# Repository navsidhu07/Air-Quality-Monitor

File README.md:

# ESP32 Air Quality Monitor

## Project Overview

An ESP32-based environmental monitoring system that measures
temperature, humidity, and relative air quality in real time.
The project was developed to provide a convenient way to
monitor environmental conditions before outdoor activities.

The system integrates a 16×2 LCD, LED status indicators, and
a Wi-Fi-enabled web dashboard. After developing a functional
breadboard prototype, a custom two-layer PCB was designed in
KiCad to integrate the hardware into a single board.

## Key Features

- Real-time temperature and humidity monitoring
- Relative air quality monitoring
- 16×2 LCD for local sensor readings
- LED-based air quality status indicators
- Wi-Fi-enabled web dashboard
- ESP32-based embedded firmware
- Custom two-layer PCB designed in KiCad
- Integrated USB-to-UART programming interface

## System Architecture

The ESP32 collects and processes environmental sensor data,
controls the LCD and LED indicators, and hosts a local web
server for wireless monitoring.

```mermaid
flowchart TD
    A[DHT22 Temperature and Humidity Sensor] --> C[ESP32]
    B[MQ-135 Gas Sensor] --> C

    C --> D[LCD1602 Display]
    C --> E[LED Status Indicators]
    C --> F[HTTP Web Server]

    F -->|Wi-Fi| G[Web Dashboard]
```

## Hardware - Prototype

A functional breadboard prototype was developed to establish
sensor functionality, microcontroller communication, and
system integration before transitioning to a custom PCB.

### Components

| Component | Purpose |
| --- | --- |
| ESP32 Development Board | Processing and wireless communication |
| DHT22 | Temperature and humidity sensing |
| MQ-135 | Gas sensing |
| LCD1602 | Local data visualization |
| Red, Yellow, and Green LEDs | Air quality status indication |
| Potentiometer | LCD contrast adjustment |
| Resistors | Current limiting and signal conditioning |

## Hardware - PCB Design

Following the development of the breadboard prototype, a
custom two-layer PCB was designed in KiCad to consolidate
the hardware into a single integrated system.

### Design Considerations

- ESP32-WROOM-32E module integration
- USB-to-UART communication using the CP2102N
- USB-C connectivity
- 5 V to 3.3 V voltage regulation
- Power supply decoupling capacitors
- Boot and reset circuitry
- Dedicated power and ground copper pours
- Sensor and display integration

### Schematic

### Front Copper Layer

### Back Copper Layer

The native KiCad project, schematic, PCB layout, and
associated symbol and footprint files are available
in the [Hardware](Hardware/) directory.

## Firmware

The firmware was developed in C++ using the Arduino
framework for the ESP32.

### Firmware Functionality

- Acquisition of temperature, humidity, and gas sensor readings
- Air quality classification logic using predefined thresholds
- Periodic LCD updates
- Control of LED status indicators
- Wi-Fi network connectivity
- HTTP web server for wireless monitoring
- JSON-based data transfer to the web dashboard

### GPIO Pin Assignments

| Component | Signal | ESP32 GPIO |
| --- | --- | --- |
| DHT22 | Data | 23 |
| MQ-135 | Analog Output | 36 |
| LCD1602 | RS | 19 |
| LCD1602 | Enable | 18 |
| LCD1602 | D4 | 17 |
| LCD1602 | D5 | 16 |
| LCD1602 | D6 | 4 |
| LCD1602 | D7 | 21 |
| Red LED | Output | 25 |
| Yellow LED | Output | 26 |
| Green LED | Output | 27 |

The firmware source code is available in the
[Firmware](Firmware/) directory.

## Web Dashboard

The ESP32 hosts a local HTTP web server that allows users
to monitor environmental conditions through a web browser.

The dashboard was developed using HTML, CSS, and JavaScript.
Sensor readings are transferred from the ESP32 to the browser
through a JSON-based HTTP endpoint.

### Dashboard Features

- Temperature and humidity visualization
- Gas sensor readings
- Color-coded air quality status indicators
- Automatic data requests every three seconds
- Real-time clock display
- Local wireless accessibility

## Testing and Validation

The breadboard prototype was developed and tested before
transitioning to the custom PCB design.

Prototype testing focused on:

- Temperature and humidity sensor readings
- Gas sensor response
- LCD functionality
- LED status indicators
- Wi-Fi connectivity
- Web dashboard functionality

The MQ-135 is used for relative air quality monitoring
rather than calibrated gas concentration or standardized
Air Quality Index (AQI) measurements.

The current firmware uses raw ADC readings from the MQ-135.
The classification thresholds require further refinement
to align with the ESP32's default ADC range. Accurate gas
concentration measurements and classification validation
remain areas for future development.

## Firmware Setup

### Requirements

- Arduino IDE
- ESP32 board package by Espressif Systems
- DHT Sensor Library by Adafruit
- Adafruit Unified Sensor library
- LiquidCrystal library by Arduino

The WiFi and WebServer libraries are included in the
ESP32 Arduino board package.

### Installation

1. Install the Arduino IDE.
2. Install the ESP32 board package through the Boards Manager.
3. Select the appropriate ESP32 development board.
4. Install the required libraries through the Library Manager.
5. Open the firmware file from the Firmware directory.
6. Replace the Wi-Fi credential placeholders with your
   local network credentials.
7. Compile and upload the firmware to the ESP32.
8. Open the Serial Monitor at a baud rate of 115200.
9. Locate the ESP32's assigned IP address.
10. Enter the IP address into a web browser connected to
    the same network.

## Repository Structure

```
Air-Quality-Monitor/
├── Firmware/
├── Hardware/
│   ├── Air Quality Monitor.kicad_pro
│   ├── Air Quality Monitor.kicad_sch
│   ├── Air Quality Monitor.kicad_pcb
│   ├── CP2102N-A02-GQFN20.kicad_sym
│   └── WFQFN-20.kicad_mod
└── README.md
```

## Project Status

The breadboard prototype, embedded firmware, and web dashboard 
have been successfully developed and tested. The custom PCB 
schematic, layout, and routing have also been completed in KiCad. 
However, PCB fabrication and assembly have not yet been pursued 
due to limited access to the necessary soldering equipment and 
assembly resources. Future development will focus on manufacturing, 
assembling, and validating the custom PCB.

## Future Improvements

- Fabricate, assemble, and validate the custom PCB
- Refine gas sensor classification thresholds and calibration
- Implement historical sensor data logging
- Improve firmware modularity
- Design a protective enclosure
- Implement non-blocking firmware timing using `millis()`

## Tools and Technologies

- KiCad
- Arduino IDE
- C++
- ESP32
- HTML
- CSS
- JavaScript
- Wi-Fi
- HTTP
- UART

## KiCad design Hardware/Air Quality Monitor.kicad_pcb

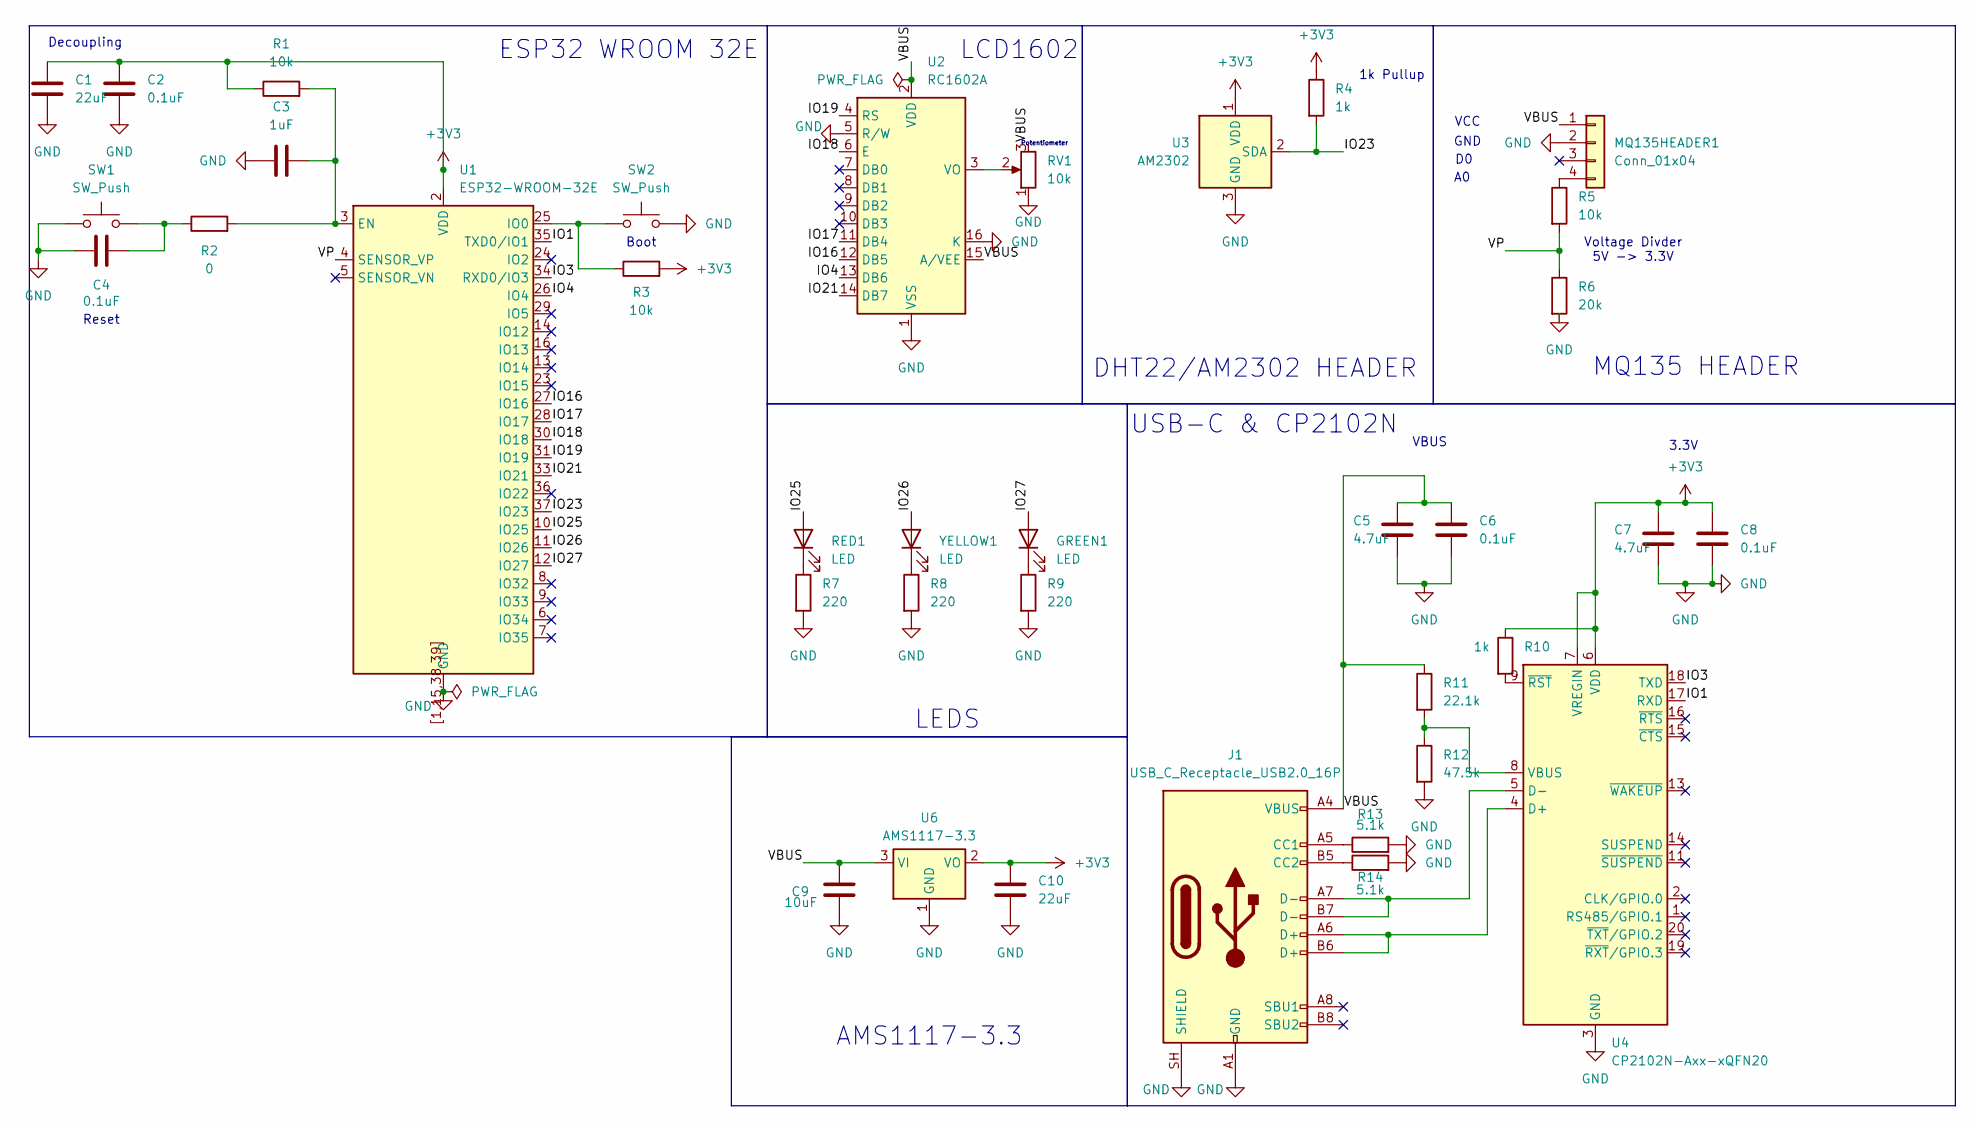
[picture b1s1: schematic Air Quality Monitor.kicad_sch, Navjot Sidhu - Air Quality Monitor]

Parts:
C1, C10: 22uF; C_0805_2012Metric
C2, C4, C6, C8: 0.1uF; C_0805_2012Metric
C3: 1uF; C_0805_2012Metric
C5, C7: 4.7uF; C_0805_2012Metric
C9: 10uF; C_0805_2012Metric
GREEN1: LED; LED_D5.0mm
J1: USB_C_Receptacle_USB2.0_16P; USB_C_Receptacle_GCT_USB4105-xx-A_16P_TopMnt_Horizontal; MPN USB4105-GF-A
MQ135HEADER1: Conn_01x04; PinHeader_1x04_P2.54mm_Vertical
R1, R3, R5: 10k; R_0805_2012Metric
R2: 0; R_0805_2012Metric
R4, R10: 1k; R_0805_2012Metric
R6: 20k; R_0805_2012Metric
R7, R8, R9: 220; R_0805_2012Metric
R11: 22.1k; R_0805_2012Metric
R12: 47.5k; R_0805_2012Metric
R13, R14: 5.1k; R_0805_2012Metric
RED1: LED; LED_D5.0mm
RV1: 10k; Potentiometer_Alps_RK09K_Single_Vertical
SW1, SW2: SW_Push; SW_SPST_B3U-3000P
U1: ESP32-WROOM-32E; MPN ESP32-WROOM-32E-N4
U2: RC1602A
U3: AM2302; ASAIR_AM2302_P2.54mm_Vertical
U4: CP2102N-Axx-xQFN20; SiliconLabs_QFN-20-1EP_3x3mm_P0.5mm_EP1.8x1.8mm_ThermalVias; MPN CP2102N-A02-GQFN20
U6: AMS1117-3.3; SOT-223-3_TabPin2; MPN AMS1117-3.3
YELLOW1: LED; LED_D5.0mm

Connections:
+3V3: C1.1, C2.1, C7.1, C8.1, C10.2, R1.1, R3.2, R4.1, R10.1, U1.2 (VDD), U3.1 (VDD), U4.6 (VDD), U4.7 (VREGIN), U6.2 (VO)
/IO1: U1.35 (TXD0/IO1), U4.17 (RXD)
/IO3: U1.34 (RXD0/IO3), U4.18 (TXD)
/IO4: U1.26 (IO4), U2.13 (DB6)
/IO16: U1.27 (IO16), U2.12 (DB5)
/IO17: U1.28 (IO17), U2.11 (DB4)
/IO18: U1.30 (IO18), U2.6 (E)
/IO19: U1.31 (IO19), U2.4 (RS)
/IO21: U1.33 (IO21), U2.14 (DB7)
/IO23: R4.2, U1.37 (IO23), U3.2 (SDA)
/IO25: RED1.2 (A), U1.10 (IO25)
/IO26: U1.11 (IO26), YELLOW1.2 (A)
/IO27: GREEN1.2 (A), U1.12 (IO27)
/VBUS: C5.1, C6.1, C9.2, J1.A4 (VBUS), J1.A9 (VBUS), J1.B4 (VBUS), J1.B9 (VBUS), MQ135HEADER1.1, R11.1, RV1.3, U2.2 (VDD), U2.15 (A/VEE), U6.3 (VI)
/VP: R5.2, R6.1, U1.4 (SENSOR_VP)
GND: C1.2, C2.2, C3.2, C4.1, C5.2, C6.2, C7.2, C8.2, C9.1, C10.1, J1.A1 (GND), J1.A12 (GND), J1.B1 (GND), J1.B12 (GND), J1.SH (SHIELD), MQ135HEADER1.2, R6.2, R7.2, R8.2, R9.2, R12.2, R13.2, R14.2, RV1.1, SW1.1, SW2.2, U1.1 (GND), U1.15 (GND), U1.38 (GND), U1.39 (GND), U1.[1,15,38,39] (GND), U2.1 (VSS), U2.5 (R/W), U2.16 (K), U3.3 (GND), U3.4 (GND), U4.3 (GND), U4.12 (GND), U4.21 (GND), U6.1 (GND)
unnamed: C4.2, R2.1, SW1.2
unnamed: GREEN1.1 (K), R9.1
unnamed: J1.A5 (CC1), R13.1
unnamed: J1.B5 (CC2), R14.1
unnamed: MQ135HEADER1.4, R5.1
unnamed: R7.1, RED1.1 (K)
unnamed: C3.1, R1.2, R2.2, U1.3 (EN)
unnamed: R3.1, SW2.1, U1.25 (IO0)
unnamed: RV1.2, U2.3 (VO)
unnamed: J1.A6 (D+), J1.B6 (D+), U4.4 (D+)
unnamed: J1.A7 (D-), J1.B7 (D-), U4.5 (D-)
unnamed: R11.2, R12.1, U4.8 (VBUS)
unnamed: R10.2, U4.9 (~RST)
unnamed: R8.1, YELLOW1.1 (K)

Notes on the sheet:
MQ135 HEADER
GND
DHT22/AM2302 HEADER
Reset
VBUS
LCD1602
Boot
LEDS
VCC
Voltage Divder 5V -> 3.3V
Potentiometer
3.3V
1k Pullup
ESP32 WROOM 32E
Decoupling
AMS1117-3.3
USB-C & CP2102N

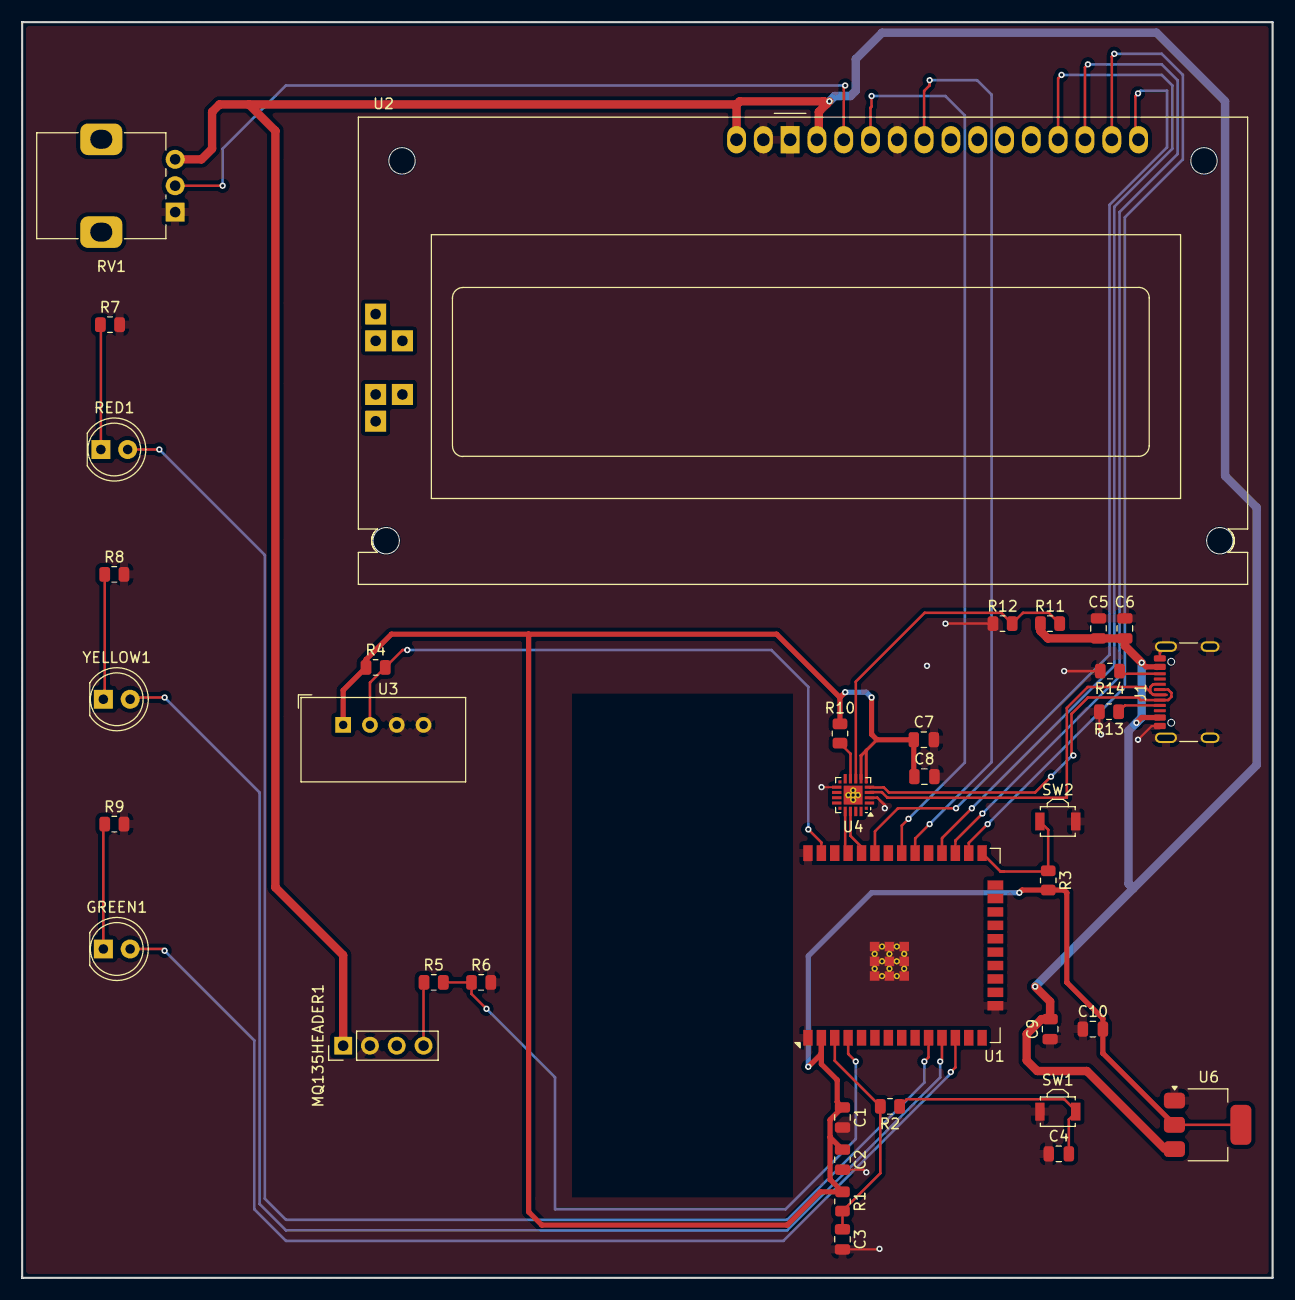
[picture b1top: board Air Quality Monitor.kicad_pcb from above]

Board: 2 copper layers, 118.5 x 119.0 mm, 37 parts (0 on the bottom side), 30 nets.
